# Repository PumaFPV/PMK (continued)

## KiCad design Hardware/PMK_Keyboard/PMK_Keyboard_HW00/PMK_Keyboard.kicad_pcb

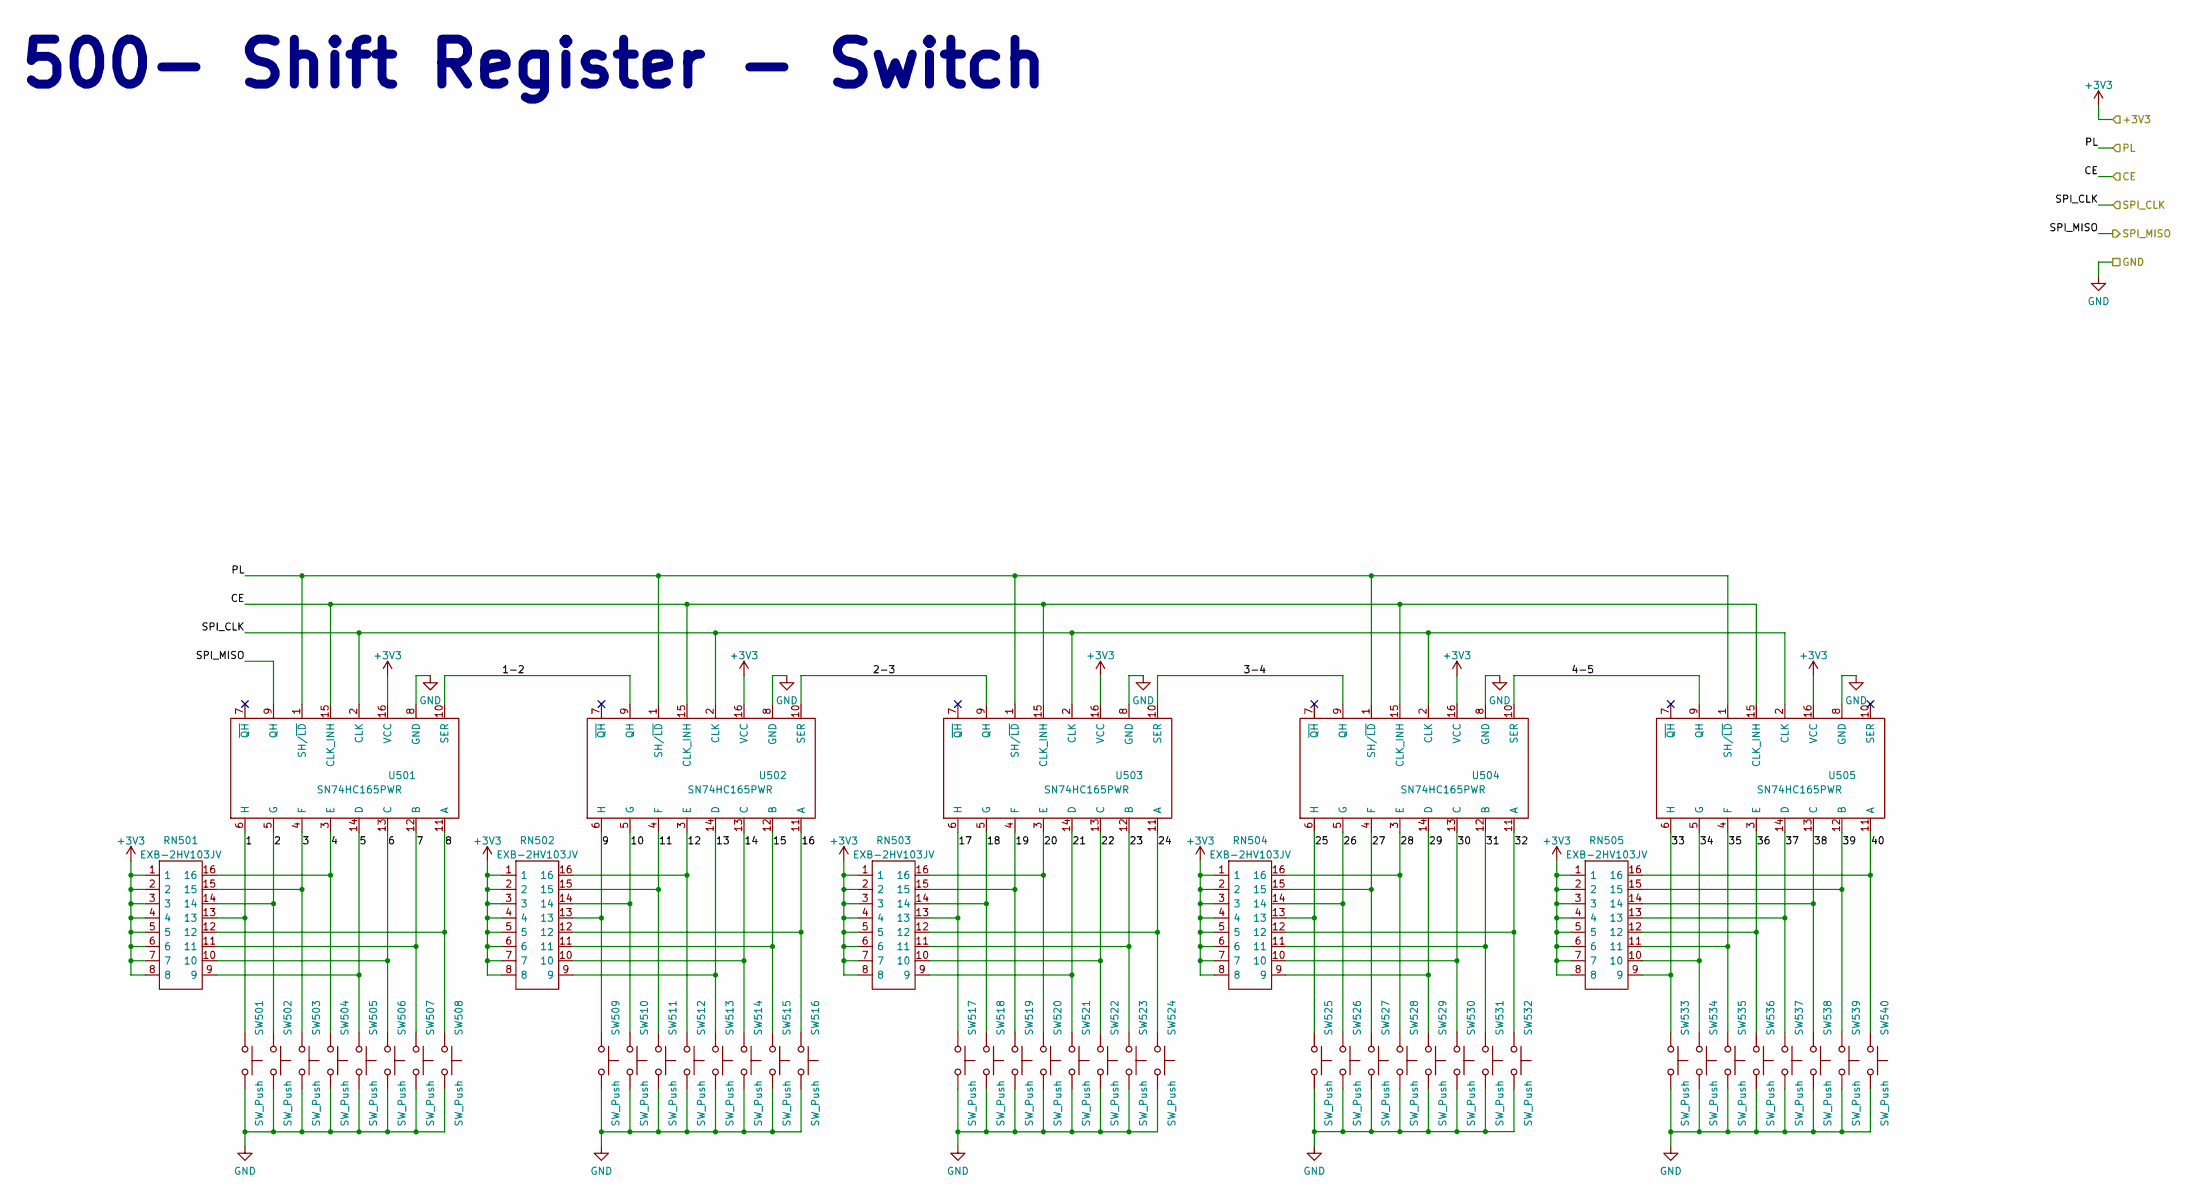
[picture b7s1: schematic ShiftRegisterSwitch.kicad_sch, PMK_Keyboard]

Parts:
RN501, RN502, RN503, RN504, RN505: EXB-2HV103JV; EXB2HV_1; Mouser Part Number 667-EXB-2HV103JV
SW501, SW502, SW503, SW504, SW505, SW506, SW507, SW508, SW509, SW510, SW511, SW512, SW513, SW514, SW515, SW516, SW517, SW518, SW519, SW520, SW521, SW522, SW523, SW524, SW525, SW526, SW527, SW528, SW529, SW530, SW531, SW532, SW533, SW534, SW535, SW536, SW537, SW538, SW539, SW540: SW_Push; Kailh_socket_PG1350_reversible
U501, U502, U503, U504, U505: SN74HC165PWR; SOP65P640X120-16N; Mouser Part Number 595-SN74HC165PWR

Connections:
+3V3: RN501.1, RN501.2, RN501.3, RN501.4, RN501.5, RN501.6, RN501.7, RN501.8, RN502.1, RN502.2, RN502.3, RN502.4, RN502.5, RN502.6, RN502.7, RN502.8, RN503.1, RN503.2, RN503.3, RN503.4, RN503.5, RN503.6, RN503.7, RN503.8, RN504.1, RN504.2, RN504.3, RN504.4, RN504.5, RN504.6, RN504.7, RN504.8, RN505.1, RN505.2, RN505.3, RN505.4, RN505.5, RN505.6, RN505.7, RN505.8, U501.16 (VCC), U502.16 (VCC), U503.16 (VCC), U504.16 (VCC), U505.16 (VCC); also elsewhere on the board
/400- ESP32S2FH4S2/PL: U501.1 (SH/~LD), U502.1 (SH/~LD), U503.1 (SH/~LD), U504.1 (SH/~LD), U505.1 (SH/~LD); also elsewhere on the board
/400- ESP32S2FH4S2/SR_CLK: U501.2 (CLK), U502.2 (CLK), U503.2 (CLK), U504.2 (CLK), U505.2 (CLK); also elsewhere on the board
/400- ESP32S2FH4S2/SR_CS: U501.15 (CLK_INH), U502.15 (CLK_INH), U503.15 (CLK_INH), U504.15 (CLK_INH), U505.15 (CLK_INH); also elsewhere on the board
/400- ESP32S2FH4S2/SR_MISO: U501.9 (QH); also elsewhere on the board
/500- Shift Register - Switch/1: RN501.13, SW501.1, U501.6 (H)
/500- Shift Register - Switch/1-2: U501.10 (SER), U502.9 (QH)
/500- Shift Register - Switch/2: RN501.14, SW502.1, U501.5 (G)
/500- Shift Register - Switch/2-3: U502.10 (SER), U503.9 (QH)
/500- Shift Register - Switch/3: RN501.15, SW503.1, U501.4 (F)
/500- Shift Register - Switch/3-4: U503.10 (SER), U504.9 (QH)
/500- Shift Register - Switch/4: RN501.16, SW504.1, U501.3 (E)
/500- Shift Register - Switch/4-5: U504.10 (SER), U505.9 (QH)
/500- Shift Register - Switch/5: RN501.9, SW505.1, U501.14 (D)
/500- Shift Register - Switch/6: RN501.10, SW506.1, U501.13 (C)
/500- Shift Register - Switch/7: RN501.11, SW507.1, U501.12 (B)
/500- Shift Register - Switch/8: RN501.12, SW508.1, U501.11 (A)
/500- Shift Register - Switch/9: RN502.13, SW509.1, U502.6 (H)
/500- Shift Register - Switch/10: RN502.14, SW510.1, U502.5 (G)
/500- Shift Register - Switch/11: RN502.15, SW511.1, U502.4 (F)
/500- Shift Register - Switch/12: RN502.16, SW512.1, U502.3 (E)
/500- Shift Register - Switch/13: RN502.9, SW513.1, U502.14 (D)
/500- Shift Register - Switch/14: RN502.10, SW514.1, U502.13 (C)
/500- Shift Register - Switch/15: RN502.11, SW515.1, U502.12 (B)
/500- Shift Register - Switch/16: RN502.12, SW516.1, U502.11 (A)
/500- Shift Register - Switch/17: RN503.13, SW517.1, U503.6 (H)
/500- Shift Register - Switch/18: RN503.14, SW518.1, U503.5 (G)
/500- Shift Register - Switch/19: RN503.15, SW519.1, U503.4 (F)
/500- Shift Register - Switch/20: RN503.16, SW520.1, U503.3 (E)
/500- Shift Register - Switch/21: RN503.9, SW521.1, U503.14 (D)
/500- Shift Register - Switch/22: RN503.10, SW522.1, U503.13 (C)
/500- Shift Register - Switch/23: RN503.11, SW523.1, U503.12 (B)
/500- Shift Register - Switch/24: RN503.12, SW524.1, U503.11 (A)
/500- Shift Register - Switch/25: RN504.13, SW525.1, U504.6 (H)
/500- Shift Register - Switch/26: RN504.14, SW526.1, U504.5 (G)
/500- Shift Register - Switch/27: RN504.15, SW527.1, U504.4 (F)
/500- Shift Register - Switch/28: RN504.16, SW528.1, U504.3 (E)
/500- Shift Register - Switch/29: RN504.9, SW529.1, U504.14 (D)
/500- Shift Register - Switch/30: RN504.10, SW530.1, U504.13 (C)
/500- Shift Register - Switch/31: RN504.11, SW531.1, U504.12 (B)
/500- Shift Register - Switch/32: RN504.12, SW532.1, U504.11 (A)
/500- Shift Register - Switch/33: RN505.9, SW533.1, U505.6 (H)
/500- Shift Register - Switch/34: RN505.10, SW534.1, U505.5 (G)
/500- Shift Register - Switch/35: RN505.11, SW535.1, U505.4 (F)
/500- Shift Register - Switch/36: RN505.12, SW536.1, U505.3 (E)
/500- Shift Register - Switch/37: RN505.13, SW537.1, U505.14 (D)
/500- Shift Register - Switch/38: RN505.14, SW538.1, U505.13 (C)
/500- Shift Register - Switch/39: RN505.15, SW539.1, U505.12 (B)
/500- Shift Register - Switch/40: RN505.16, SW540.1, U505.11 (A)
GND: SW501.2, SW502.2, SW503.2, SW504.2, SW505.2, SW506.2, SW507.2, SW508.2, SW509.2, SW510.2, SW511.2, SW512.2, SW513.2, SW514.2, SW515.2, SW516.2, SW517.2, SW518.2, SW519.2, SW520.2, SW521.2, SW522.2, SW523.2, SW524.2, SW525.2, SW526.2, SW527.2, SW528.2, SW529.2, SW530.2, SW531.2, SW532.2, SW533.2, SW534.2, SW535.2, SW536.2, SW537.2, SW538.2, SW539.2, SW540.2, U501.8 (GND), U502.8 (GND), U503.8 (GND), U504.8 (GND), U505.8 (GND); also elsewhere on the board

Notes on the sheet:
500- Shift Register - Switch

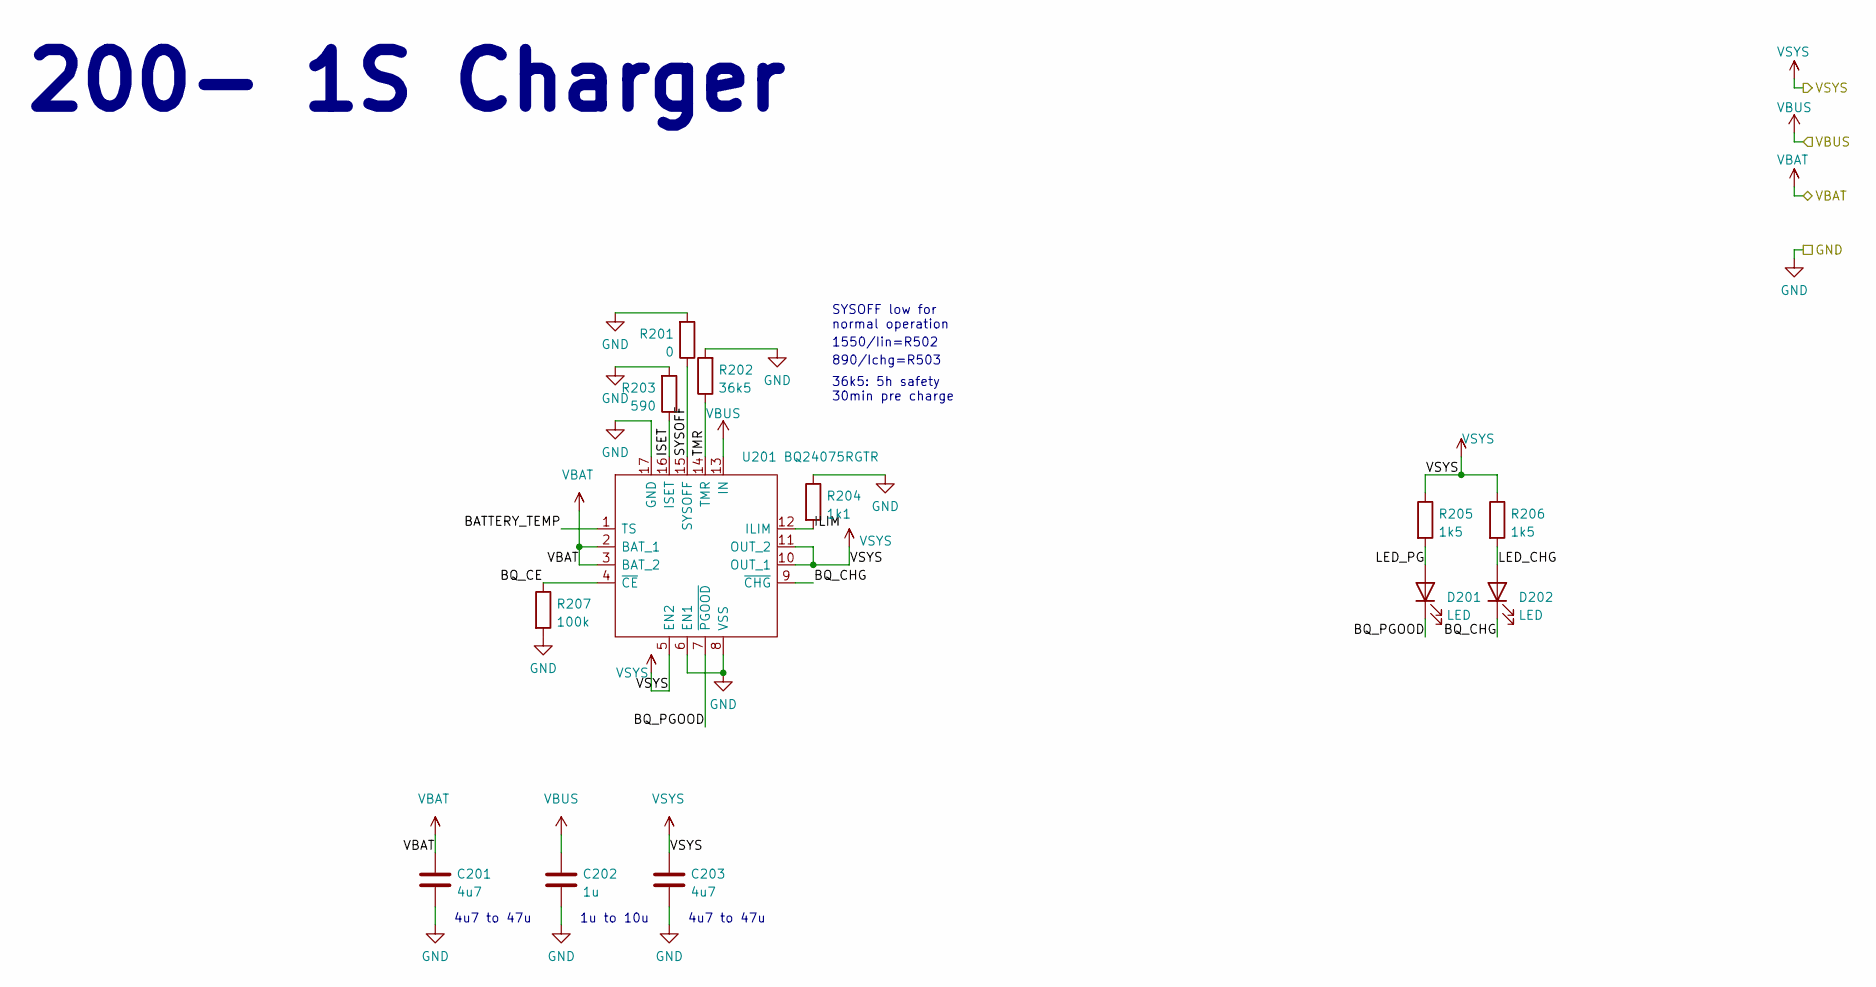
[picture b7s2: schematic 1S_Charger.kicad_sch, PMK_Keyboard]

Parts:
C201, C203: 4u7; C_0603_1608Metric
C202: 1u; C_0603_1608Metric
D201, D202: LED; LED_0402_1005Metric_DUALSIDE
R201: 0; R_0402_1005Metric
R202: 36k5; R_0402_1005Metric
R203: 590; R_0402_1005Metric
R204: 1k1; R_0402_1005Metric
R205, R206: 1k5; R_0402_1005Metric
R207: 100k; R_0402_1005Metric
U201: BQ24075RGTR; QFN50P300X300X100-17N-D; Mouser Part Number 595-BQ24075RGTR

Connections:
/100- Connectors/VBAT: C201.1, U201.2 (BAT_1), U201.3 (BAT_2); also elsewhere on the board
/200- 1S_Charger/BATTERY_TEMP: U201.1 (TS); also elsewhere on the board
/200- 1S_Charger/BQ_CE: R207.1, U201.4 (~CE)
/200- 1S_Charger/BQ_CHG: D202.1 (K), U201.9 (~CHG)
/200- 1S_Charger/BQ_PGOOD: D201.1 (K), U201.7 (~PGOOD)
/200- 1S_Charger/ILIM: R204.2, U201.12 (ILIM)
/200- 1S_Charger/ISET: R203.1, U201.16 (ISET)
/200- 1S_Charger/LED_CHG: D202.2 (A), R206.2
/200- 1S_Charger/LED_PG: D201.2 (A), R205.2
/200- 1S_Charger/SYSOFF: R201.1, U201.15 (SYSOFF)
/200- 1S_Charger/TMR: R202.1, U201.14 (TMR)
/VSYS: C203.1, R205.1, R206.1, U201.5 (EN2), U201.10 (OUT_1), U201.11 (OUT_2); also elsewhere on the board
GND: C201.2, C202.2, C203.2, R201.2, R202.2, R203.2, R204.1, R207.2, U201.6 (EN1), U201.8 (VSS), U201.17 (GND); also elsewhere on the board
VBUS: C202.1, U201.13 (IN); also elsewhere on the board

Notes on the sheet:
890/Ichg=R503
200- 1S Charger
4u7 to 47u
1u to 10u
SYSOFF low for normal operation
36k5: 5h safety 30min pre charge
1550/Iin=R502

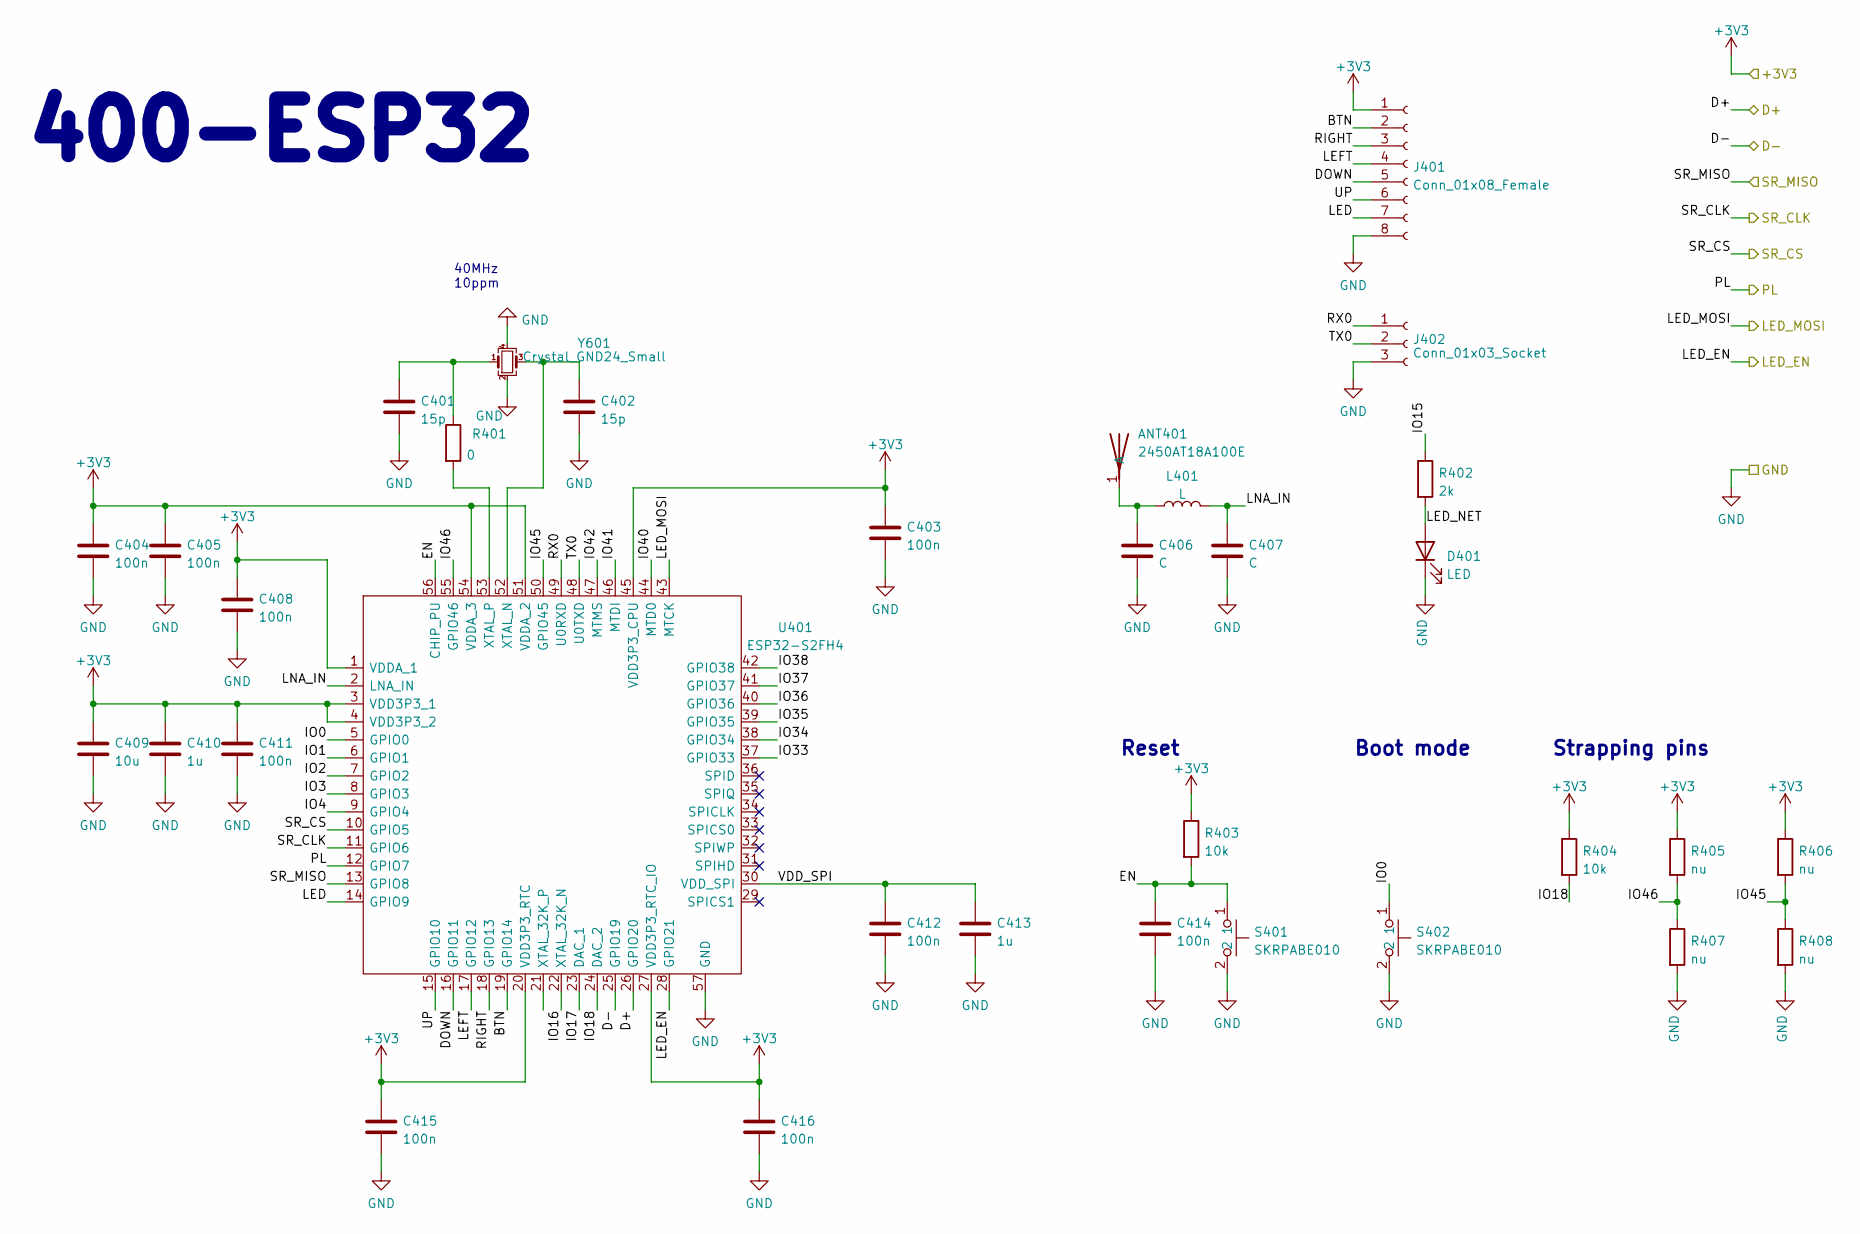
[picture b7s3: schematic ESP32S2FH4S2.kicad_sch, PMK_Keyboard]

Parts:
ANT401: 2450AT18A100E; ANTC3216X140N; Mouser Part Number 609-2450AT18A100E
C401, C402: 15p; C_0201_0603Metric
C403, C404, C405, C408, C411, C412, C414, C415, C416: 100n; C_0402_1005Metric
C406, C407: C; C_0201_0603Metric
C409: 10u; C_0603_1608Metric
C410, C413: 1u; C_0402_1005Metric
D401: LED; LED_0402_1005Metric_DUALSIDE
J401: Conn_01x08_Female; PinHeader_1x08_P1.27mm_Vertical
J402: Conn_01x03_Socket; PinHeader_1x03_P2.54mm_Vertical
L401: L; L_0201_0603Metric
R401: 0; R_0201_0603Metric
R402: 2k; R_0402_1005Metric
R403, R404: 10k; R_0201_0603Metric
R405, R406, R407, R408: nu; R_0201_0603Metric
S401, S402: SKRPABE010; Mouser Part Number 688-SKRPAB
U401: ESP32-S2FH4; QFN40P700X700X90-57N-D; Mouser Part Number 356-ESP32-S2FH4
Y601: Crystal_GND24_Small; Crystal_SMD_2016-4Pin_2.0x1.6mm

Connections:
+3V3: C403.1, C404.1, C405.1, C408.1, C409.1, C410.1, C411.1, C415.1, C416.1, J401.1, R403.1, R404.1, R405.1, R406.1, U401.1 (VDDA_1), U401.3 (VDD3P3_1), U401.4 (VDD3P3_2), U401.20 (VDD3P3_RTC), U401.27 (VDD3P3_RTC_IO), U401.45 (VDD3P3_CPU), U401.51 (VDDA_2), U401.54 (VDDA_3); also elsewhere on the board
/100- Connectors/D+: U401.26 (GPIO20); also elsewhere on the board
/100- Connectors/D-: U401.25 (GPIO19); also elsewhere on the board
/300- Power/LED_EN: U401.28 (GPIO21); also elsewhere on the board
/400- ESP32S2FH4S2/BTN: J401.2, U401.19 (GPIO14)
/400- ESP32S2FH4S2/DOWN: J401.5, U401.16 (GPIO11)
/400- ESP32S2FH4S2/EN: C414.1, R403.2, S401.1, U401.56 (CHIP_PU)
/400- ESP32S2FH4S2/IO0: S402.1, U401.5 (GPIO0)
/400- ESP32S2FH4S2/IO1: U401.6 (GPIO1)
/400- ESP32S2FH4S2/IO2: U401.7 (GPIO2)
/400- ESP32S2FH4S2/IO3: U401.8 (GPIO3)
/400- ESP32S2FH4S2/IO4: U401.9 (GPIO4)
/400- ESP32S2FH4S2/IO15: R402.1
/400- ESP32S2FH4S2/IO16: U401.22 (XTAL_32K_N)
/400- ESP32S2FH4S2/IO17: U401.23 (DAC_1)
/400- ESP32S2FH4S2/IO18: R404.2, U401.24 (DAC_2)
/400- ESP32S2FH4S2/IO33: U401.37 (GPIO33)
/400- ESP32S2FH4S2/IO34: U401.38 (GPIO34)
/400- ESP32S2FH4S2/IO35: U401.39 (GPIO35)
/400- ESP32S2FH4S2/IO36: U401.40 (GPIO36)
/400- ESP32S2FH4S2/IO37: U401.41 (GPIO37)
/400- ESP32S2FH4S2/IO38: U401.42 (GPIO38)
/400- ESP32S2FH4S2/IO40: U401.44 (MTD0)
/400- ESP32S2FH4S2/IO41: U401.46 (MTDI)
/400- ESP32S2FH4S2/IO42: U401.47 (MTMS)
/400- ESP32S2FH4S2/IO45: R406.2, R408.1, U401.50 (GPIO45)
/400- ESP32S2FH4S2/IO46: R405.2, R407.1, U401.55 (GPIO46)
/400- ESP32S2FH4S2/LED: J401.7, U401.14 (GPIO9)
/400- ESP32S2FH4S2/LED_MOSI: U401.43 (MTCK); also elsewhere on the board
/400- ESP32S2FH4S2/LED_NET: D401.2 (A), R402.2
/400- ESP32S2FH4S2/LEFT: J401.4, U401.17 (GPIO12)
/400- ESP32S2FH4S2/LNA_IN: C407.1, L401.2, U401.2 (LNA_IN)
/400- ESP32S2FH4S2/PL: U401.12 (GPIO7); also elsewhere on the board
/400- ESP32S2FH4S2/RIGHT: J401.3, U401.18 (GPIO13)
/400- ESP32S2FH4S2/RX0: J402.1, U401.49 (U0RXD)
/400- ESP32S2FH4S2/SR_CLK: U401.11 (GPIO6); also elsewhere on the board
/400- ESP32S2FH4S2/SR_CS: U401.10 (GPIO5); also elsewhere on the board
/400- ESP32S2FH4S2/SR_MISO: U401.13 (GPIO8); also elsewhere on the board
/400- ESP32S2FH4S2/TX0: J402.2, U401.48 (U0TXD)
/400- ESP32S2FH4S2/UP: J401.6, U401.15 (GPIO10)
/400- ESP32S2FH4S2/VDD_SPI: C412.1, C413.1, U401.30 (VDD_SPI)
GND: C401.2, C402.2, C403.2, C404.2, C405.2, C406.2, C407.2, C408.2, C409.2, C410.2, C411.2, C412.2, C413.2, C414.2, C415.2, C416.2, D401.1 (K), J401.8, J402.3, R407.2, R408.2, S401.2, S402.2, U401.57 (GND), Y601.2, Y601.4; also elsewhere on the board
unnamed: ANT401.1 (A), C406.1, L401.1
unnamed: C401.1, R401.1, Y601.1
unnamed: C402.1, U401.52 (XTAL_N), Y601.3
unnamed: R401.2, U401.53 (XTAL_P)

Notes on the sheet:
Boot mode
Reset
40MHz 10ppm
400-ESP32
Strapping pins

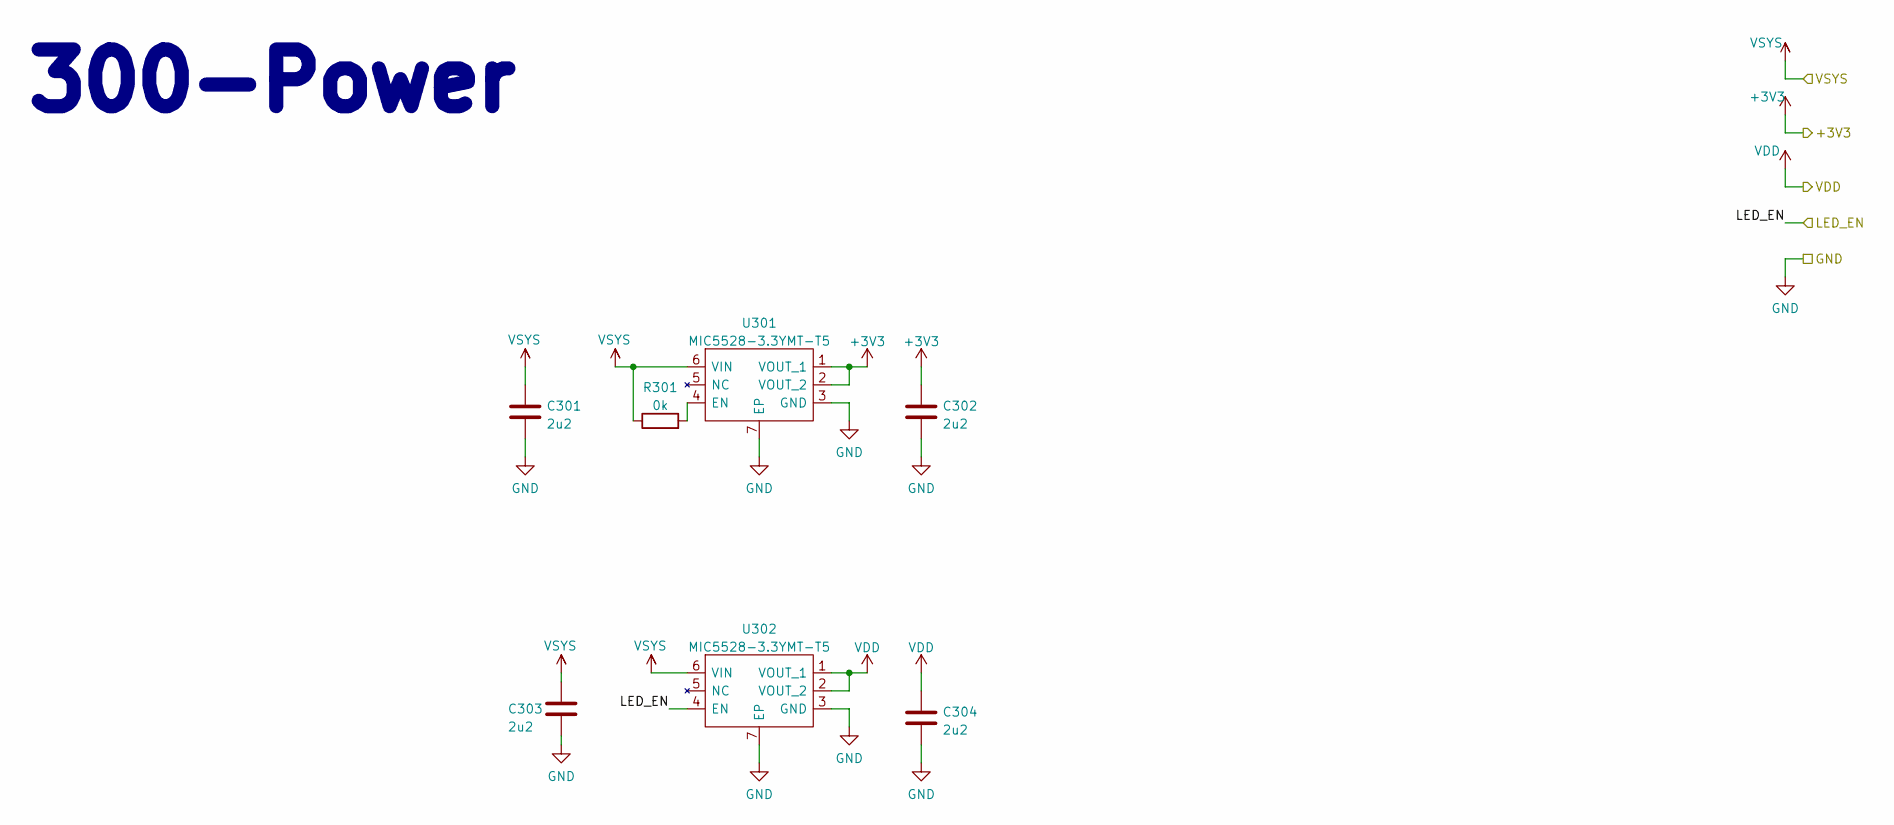
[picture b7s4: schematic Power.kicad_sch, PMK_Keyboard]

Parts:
C301, C302, C303, C304: 2u2; C_0603_1608Metric
R301: 0k; R_0201_0603Metric
U301, U302: MIC5528-3.3YMT-T5; SON40P120X120X60-7N-D; Mouser Part Number 998-MIC5528-3.3YMTT5

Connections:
+3V3: C302.1, U301.1 (VOUT_1), U301.2 (VOUT_2); also elsewhere on the board
/300- Power/LED_EN: U302.4 (EN); also elsewhere on the board
/300- Power/PRIM_LDO_EN: R301.2, U301.4 (EN)
/VSYS: C301.1, C303.1, R301.1, U301.6 (VIN), U302.6 (VIN); also elsewhere on the board
GND: C301.2, C302.2, C303.2, C304.2, U301.3 (GND), U301.7 (EP), U302.3 (GND), U302.7 (EP); also elsewhere on the board
VDD: C304.1, U302.1 (VOUT_1), U302.2 (VOUT_2); also elsewhere on the board

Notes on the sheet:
300-Power

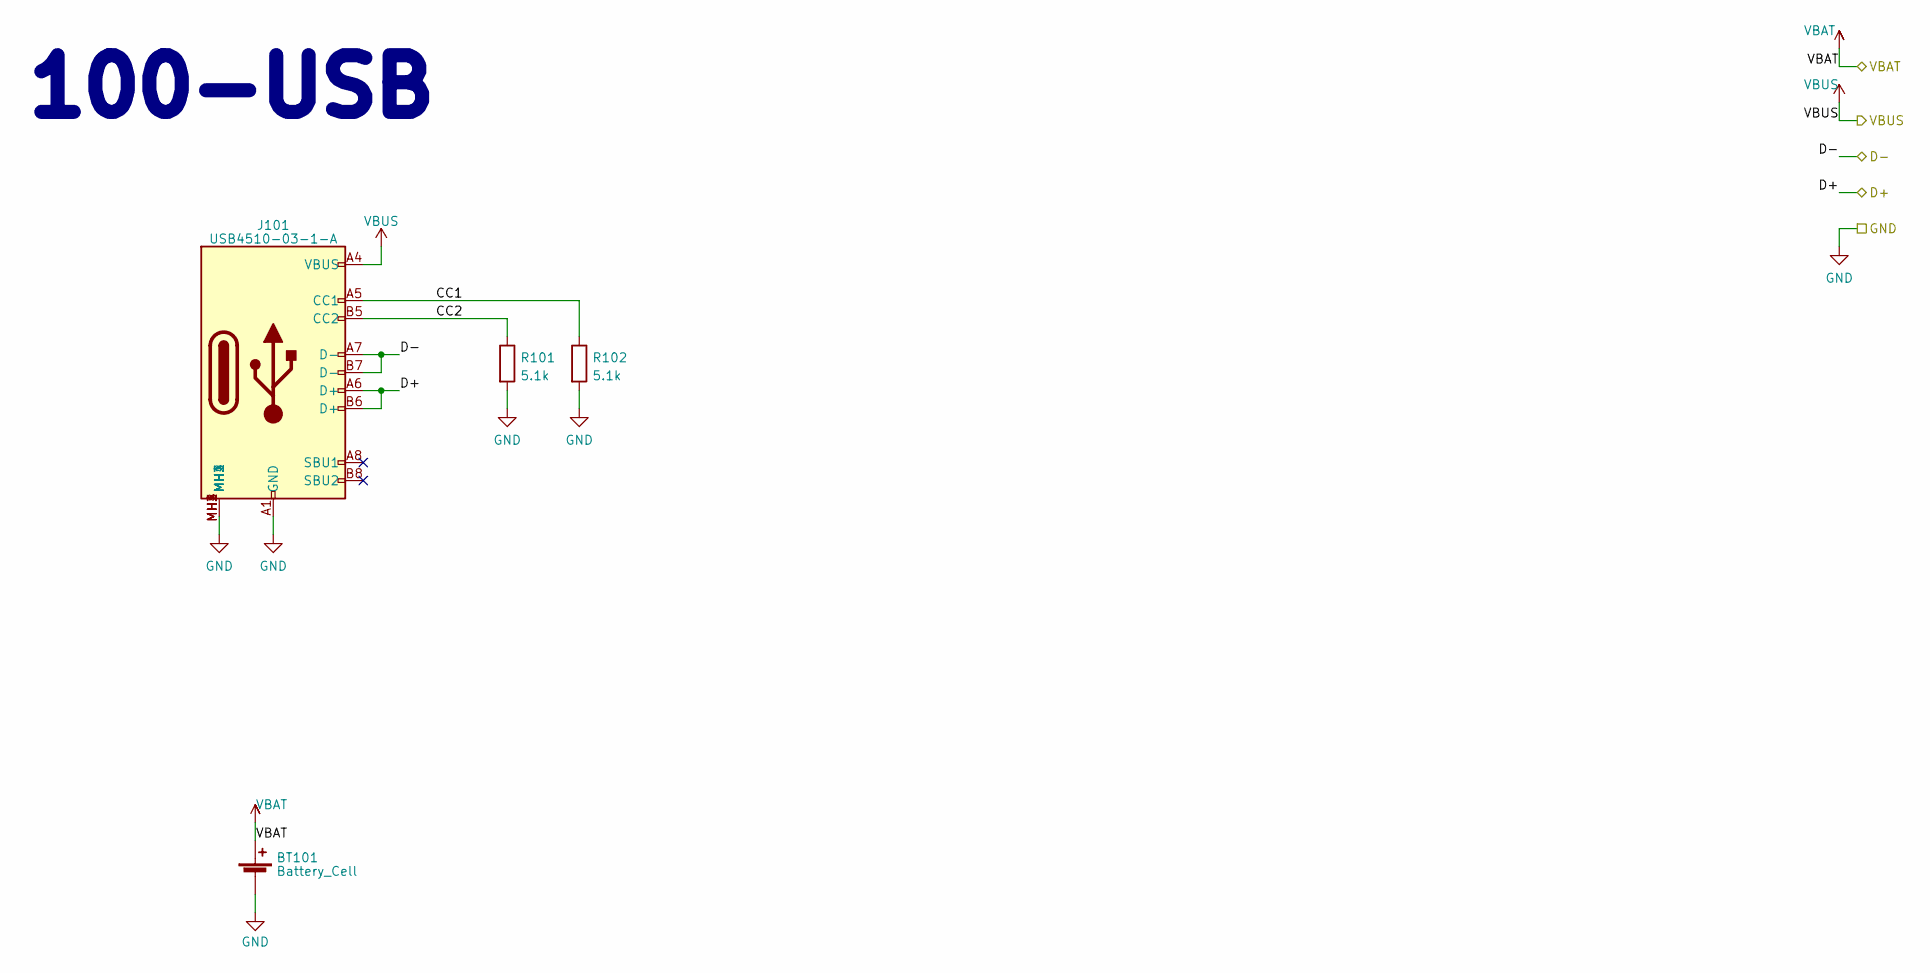
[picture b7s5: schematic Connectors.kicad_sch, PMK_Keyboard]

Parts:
BT101: Battery_Cell; BatteryHolder_Keystone_1042_1x18650_DUALSIDE
J101: USB4510-03-1-A; USB4510031A; Mouser Part Number 640-USB4510031A
R101, R102: 5.1k; R_0201_0603Metric

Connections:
/100- Connectors/CC1: J101.A5 (CC1), R102.1
/100- Connectors/CC2: J101.B5 (CC2), R101.1
/100- Connectors/D+: J101.A6 (D+), J101.B6 (D+); also elsewhere on the board
/100- Connectors/D-: J101.A7 (D-), J101.B7 (D-); also elsewhere on the board
/100- Connectors/VBAT: BT101.1 (+); also elsewhere on the board
GND: BT101.2 (-), J101.A1 (GND), J101.A12 (GND), J101.B1 (GND), J101.B12 (GND), J101.MH1, J101.MH2, J101.MH3, J101.MH4, R101.2, R102.2; also elsewhere on the board
VBUS: J101.A4 (VBUS), J101.A9 (VBUS), J101.B4 (VBUS), J101.B9 (VBUS); also elsewhere on the board

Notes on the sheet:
100-USB

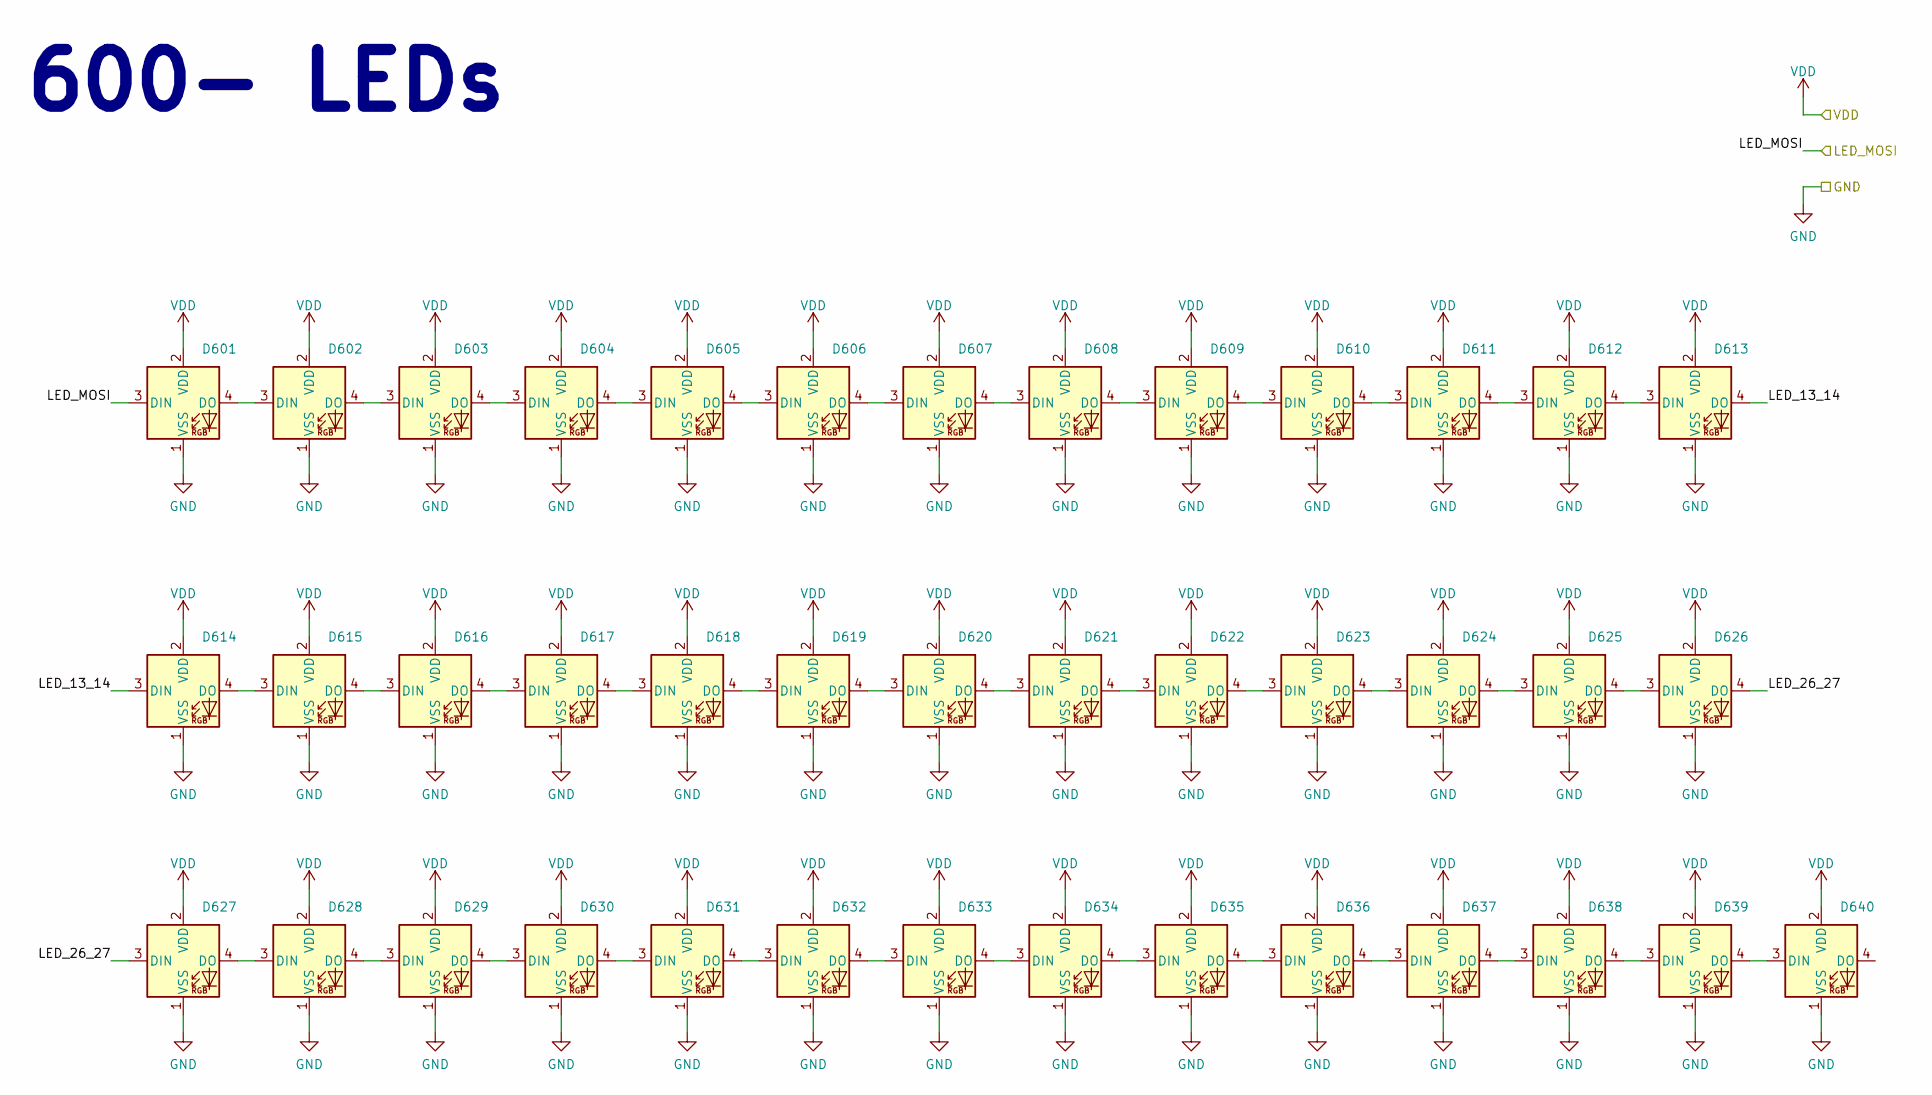
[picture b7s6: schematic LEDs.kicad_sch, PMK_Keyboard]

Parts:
D601, D602, D603, D604, D605, D606, D607, D608, D609, D610, D611, D612, D613, D614, D615, D616, D617, D618, D619, D620, D621, D622, D623, D624, D625, D626, D627, D628, D629, D630, D631, D632, D633, D634, D635, D636, D637, D638, D639, D640: YF923_2020_WS2812_LED; YF923_2020_WS2812_LED_DUALSIDE

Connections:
/400- ESP32S2FH4S2/LED_MOSI: D601.3 (DIN); also elsewhere on the board
/600- LEDs/LED_13_14: D613.4 (DO), D614.3 (DIN)
/600- LEDs/LED_26_27: D626.4 (DO), D627.3 (DIN)
GND: D601.1 (VSS), D602.1 (VSS), D603.1 (VSS), D604.1 (VSS), D605.1 (VSS), D606.1 (VSS), D607.1 (VSS), D608.1 (VSS), D609.1 (VSS), D610.1 (VSS), D611.1 (VSS), D612.1 (VSS), D613.1 (VSS), D614.1 (VSS), D615.1 (VSS), D616.1 (VSS), D617.1 (VSS), D618.1 (VSS), D619.1 (VSS), D620.1 (VSS), D621.1 (VSS), D622.1 (VSS), D623.1 (VSS), D624.1 (VSS), D625.1 (VSS), D626.1 (VSS), D627.1 (VSS), D628.1 (VSS), D629.1 (VSS), D630.1 (VSS), D631.1 (VSS), D632.1 (VSS), D633.1 (VSS), D634.1 (VSS), D635.1 (VSS), D636.1 (VSS), D637.1 (VSS), D638.1 (VSS), D639.1 (VSS), D640.1 (VSS); also elsewhere on the board
unnamed: D601.4 (DO), D602.3 (DIN)
unnamed: D602.4 (DO), D603.3 (DIN)
unnamed: D603.4 (DO), D604.3 (DIN)
unnamed: D604.4 (DO), D605.3 (DIN)
unnamed: D605.4 (DO), D606.3 (DIN)
unnamed: D606.4 (DO), D607.3 (DIN)
unnamed: D607.4 (DO), D608.3 (DIN)
unnamed: D608.4 (DO), D609.3 (DIN)
unnamed: D609.4 (DO), D610.3 (DIN)
unnamed: D610.4 (DO), D611.3 (DIN)
unnamed: D611.4 (DO), D612.3 (DIN)
unnamed: D612.4 (DO), D613.3 (DIN)
unnamed: D614.4 (DO), D615.3 (DIN)
unnamed: D615.4 (DO), D616.3 (DIN)
unnamed: D616.4 (DO), D617.3 (DIN)
unnamed: D617.4 (DO), D618.3 (DIN)
unnamed: D618.4 (DO), D619.3 (DIN)
unnamed: D619.4 (DO), D620.3 (DIN)
unnamed: D620.4 (DO), D621.3 (DIN)
unnamed: D621.4 (DO), D622.3 (DIN)
unnamed: D622.4 (DO), D623.3 (DIN)
unnamed: D623.4 (DO), D624.3 (DIN)
unnamed: D624.4 (DO), D625.3 (DIN)
unnamed: D625.4 (DO), D626.3 (DIN)
unnamed: D627.4 (DO), D628.3 (DIN)
unnamed: D628.4 (DO), D629.3 (DIN)
unnamed: D629.4 (DO), D630.3 (DIN)
unnamed: D630.4 (DO), D631.3 (DIN)
unnamed: D631.4 (DO), D632.3 (DIN)
unnamed: D632.4 (DO), D633.3 (DIN)
unnamed: D633.4 (DO), D634.3 (DIN)
unnamed: D634.4 (DO), D635.3 (DIN)
unnamed: D635.4 (DO), D636.3 (DIN)
unnamed: D636.4 (DO), D637.3 (DIN)
unnamed: D637.4 (DO), D638.3 (DIN)
unnamed: D638.4 (DO), D639.3 (DIN)
unnamed: D639.4 (DO), D640.3 (DIN)
VDD: D601.2 (VDD), D602.2 (VDD), D603.2 (VDD), D604.2 (VDD), D605.2 (VDD), D606.2 (VDD), D607.2 (VDD), D608.2 (VDD), D609.2 (VDD), D610.2 (VDD), D611.2 (VDD), D612.2 (VDD), D613.2 (VDD), D614.2 (VDD), D615.2 (VDD), D616.2 (VDD), D617.2 (VDD), D618.2 (VDD), D619.2 (VDD), D620.2 (VDD), D621.2 (VDD), D622.2 (VDD), D623.2 (VDD), D624.2 (VDD), D625.2 (VDD), D626.2 (VDD), D627.2 (VDD), D628.2 (VDD), D629.2 (VDD), D630.2 (VDD), D631.2 (VDD), D632.2 (VDD), D633.2 (VDD), D634.2 (VDD), D635.2 (VDD), D636.2 (VDD), D637.2 (VDD), D638.2 (VDD), D639.2 (VDD), D640.2 (VDD); also elsewhere on the board

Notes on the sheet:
600- LEDs
